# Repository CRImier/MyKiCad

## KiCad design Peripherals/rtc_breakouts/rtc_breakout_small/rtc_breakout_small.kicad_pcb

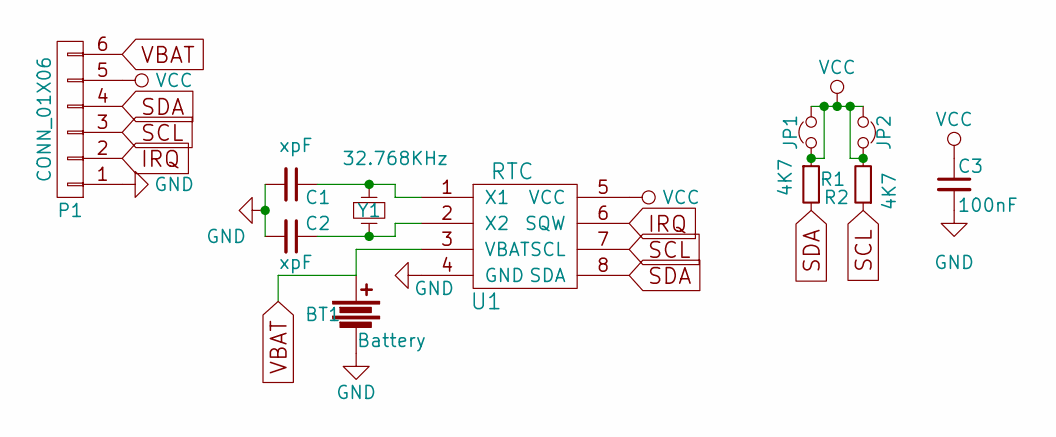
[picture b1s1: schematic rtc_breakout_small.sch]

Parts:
BT1: Battery; CR2032H
C1, C2: xpF; C_0603_HandSoldering
C3: 100nF; C_0603_HandSoldering
JP1, JP2: Jumper_NC_Small; GS2_SMALL
P1: CONN_01X06; Pin_Header_Straight_1x06_Pitch2.54mm
R1, R2: 4K7; R_0603_HandSoldering
U1: RTC; SOIC-8_3.9x4.9mm_Pitch1.27mm
Y1: 32.768KHz; Crystal_SMD_G8-2pin_3.2x1.5mm_HandSoldering

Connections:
GND: BT1.2, C1.2, C2.2, C3.2, P1.1, U1.4 (GND)
IRQ: P1.2, U1.6 (SQW)
unnamed: C1.1, U1.1 (X1), Y1.1
unnamed: C2.1, U1.2 (X2), Y1.2
SCL: P1.3, R2.1, U1.7 (SCL)
SDA: P1.4, R1.2, U1.8 (SDA)
VBAT: BT1.1, P1.6, U1.3 (VBAT)
VCC: C3.1, JP1.1, JP1.2, JP2.1, JP2.2, P1.5, R1.1, R2.2, U1.5 (VCC)

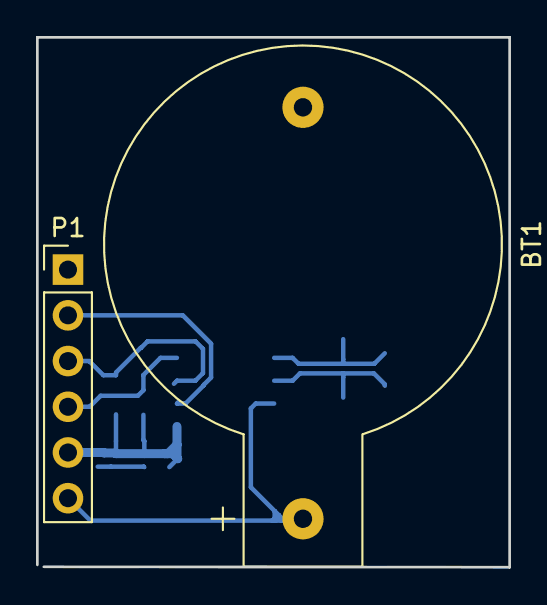
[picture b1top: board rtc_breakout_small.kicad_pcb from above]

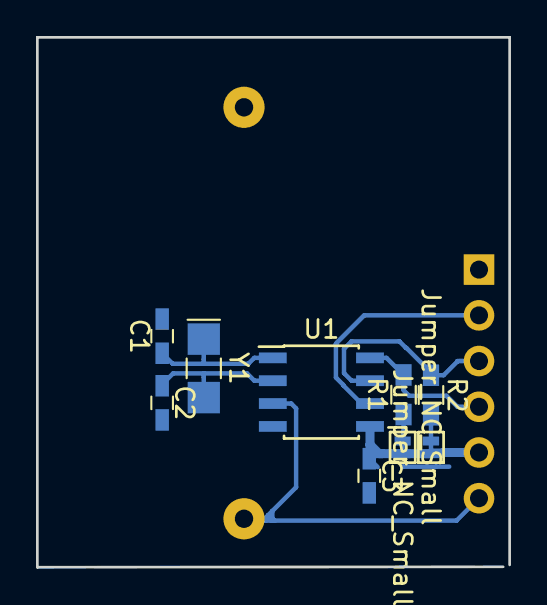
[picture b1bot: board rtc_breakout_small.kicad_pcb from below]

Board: 2 copper layers, 26.2 x 29.4 mm, 11 parts (9 on the bottom side), 8 nets.

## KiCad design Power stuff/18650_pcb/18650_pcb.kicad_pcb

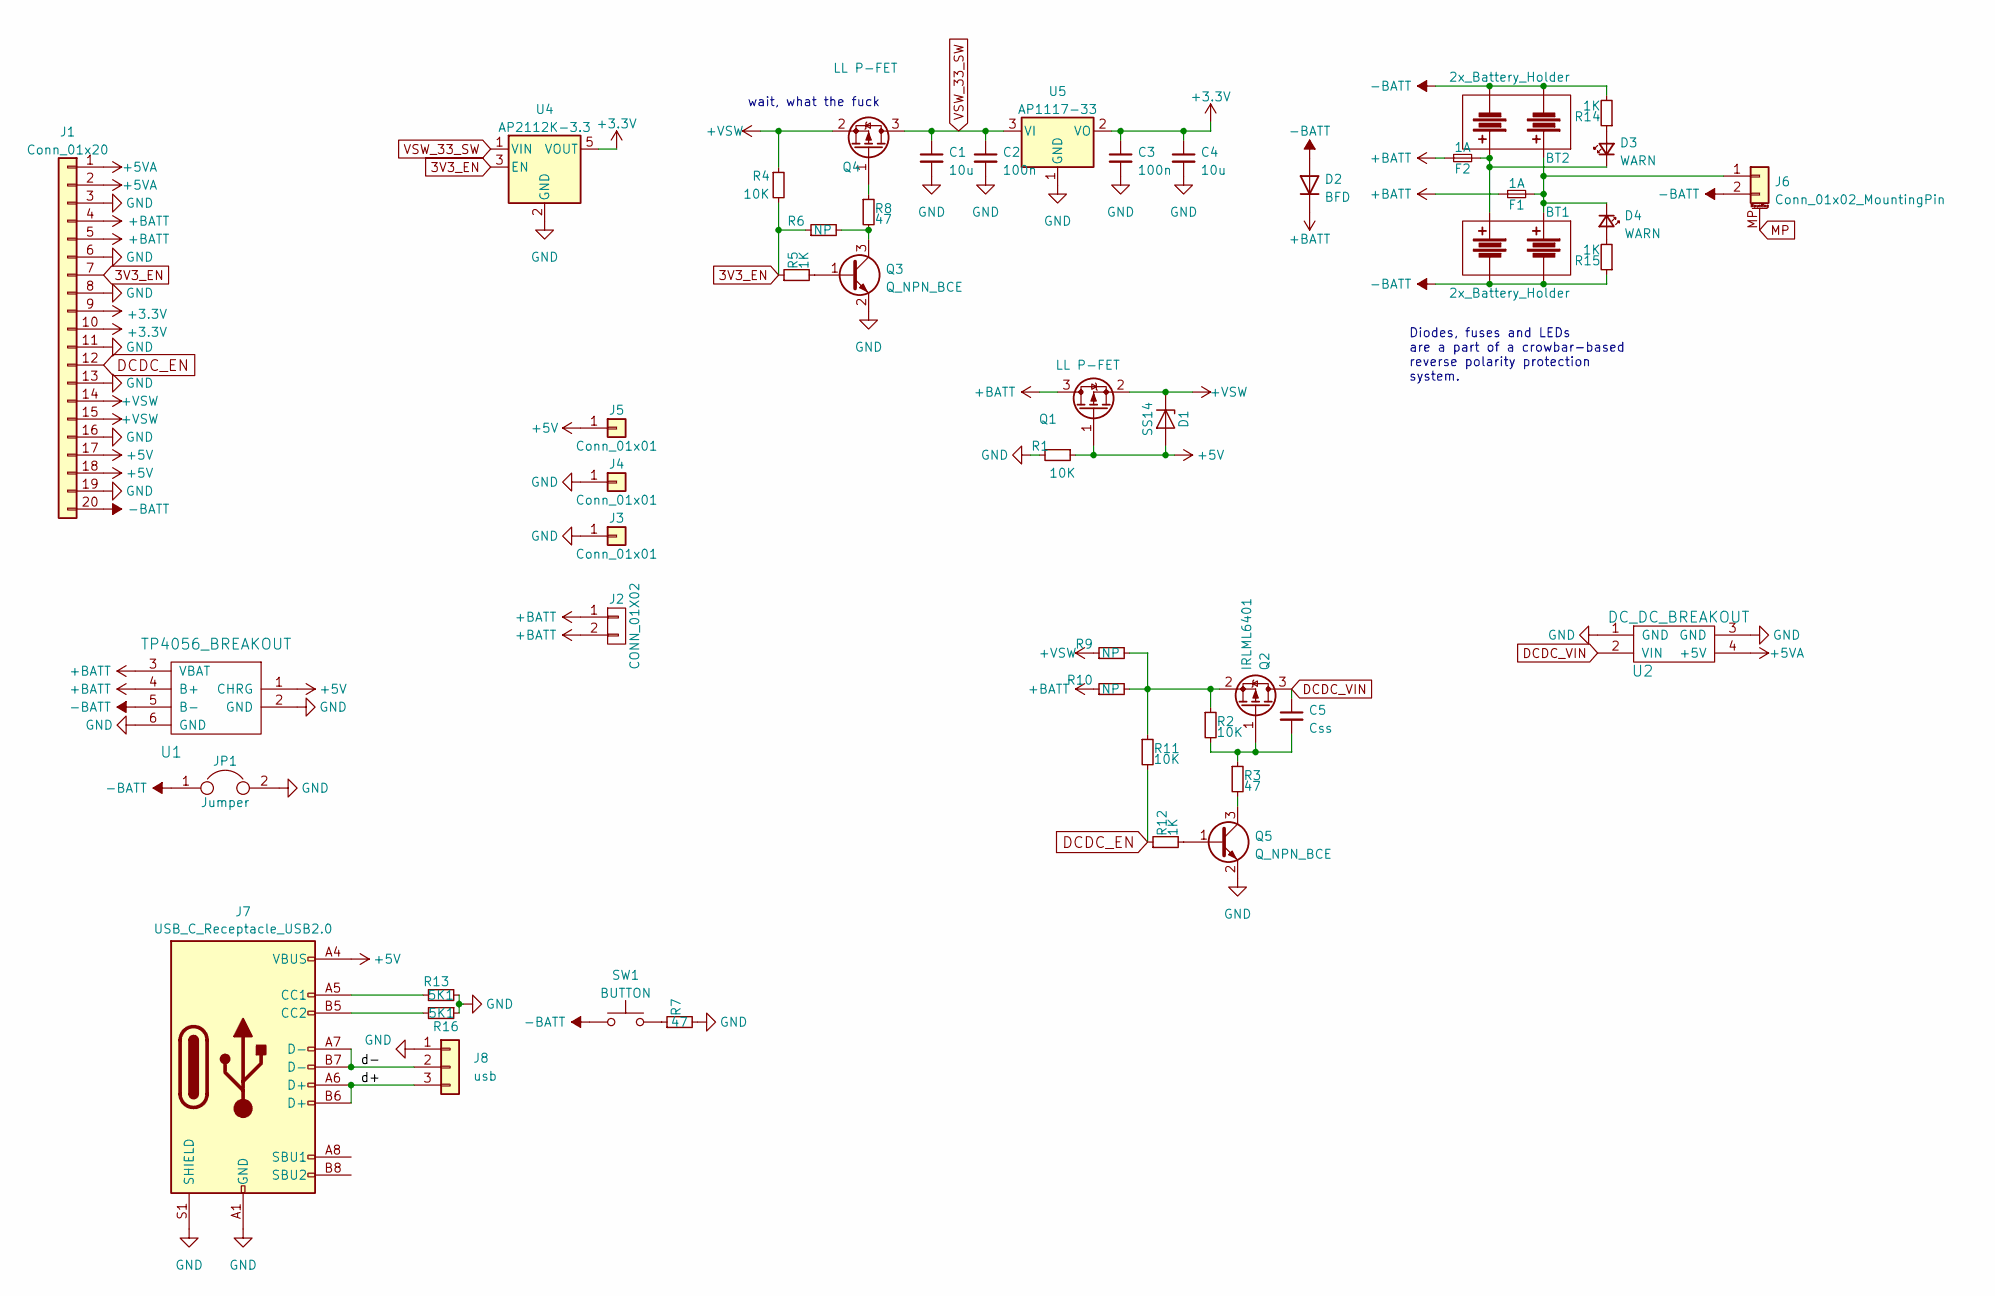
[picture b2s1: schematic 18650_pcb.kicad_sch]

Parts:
BT1: 2x_Battery_Holder; KEYSTONE_1048
BT2: 2x_Battery_Holder; BLM_18650_PC4
C1, C4: 10u; C_0805_2012Metric
C2, C3: 100n; C_0805_2012Metric
C5: Css; C_0805_2012Metric
D1: SS14; D_SMA_Handsoldering
D2: BFD; D_SMC-RM10_Universal_Handsoldering
D3, D4: WARN; LED_0805_2012Metric
F1, F2: 1A; Fuse_2010_5025Metric_Pad1.52x2.65mm_HandSolder
J1: Conn_01x20; PinHeader_1x20_P2.54mm_Vertical
J2: CONN_01X02; PinHeader_1x02_P2.54mm_Vertical
J3, J4, J5: Conn_01x01; PinHeader_1x01_P2.54mm_Vertical
J6: Conn_01x02_MountingPin; JST_PH_S2B-PH-SM4-TB_02x2.00mm_Angled
J7: USB_C_Receptacle_USB2.0; USB_C_Receptacle_HRO_TYPE-C-31-M-12
J8: usb; PinHeader_1x03_P2.54mm_Vertical
JP1: Jumper; GS2
Q1, Q4: LL P-FET; SOT-23
Q2: IRLML6401; SOT-23
Q3, Q5: Q_NPN_BCE; SOT-23
R1, R2, R4, R11: 10K; R_0805_2012Metric
R3, R7, R8: 47; R_0805_2012Metric
R5, R12, R14, R15: 1K; R_0805_2012Metric
R6, R9, R10: NP; R_0805_2012Metric
R13, R16: 5K1; R_0805_2012Metric
SW1: BUTTON; Switch_Side_Vertical_Combined
U1: TP4056_BREAKOUT
U2: DC_DC_BREAKOUT; DC-DC-BREAKOUT
U4: AP2112K-3.3; SOT-23-5
U5: AP1117-33; SOT-223-3_TabPin2

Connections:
3V3_EN: J1.7, R4.2, R5.1, R6.1, U4.3 (EN)
+3.3V: C3.1, C4.1, J1.9, J1.10, U4.5 (VOUT), U5.2 (VO)
+5V: D1.2 (A), J1.17, J1.18, J5.1, J7.A4 (VBUS), J7.A9 (VBUS), J7.B4 (VBUS), J7.B9 (VBUS), Q1.1 (G), R1.1, U1.1 (CHRG)
+5VA: J1.1, J1.2, U2.4 (+5V)
+BATT: D2.1 (K), F1.1, F2.1, J1.4, J1.5, J2.1, J2.2, Q1.3 (D), R10.1, U1.3 (VBAT), U1.4 (B+)
+VSW: D1.1 (K), J1.14, J1.15, Q1.2 (S), Q4.2 (S), R4.1, R9.1
-BATT: BT1.3, BT1.4, BT2.3, BT2.4, D2.2 (A), J1.20, J6.2, JP1.1, R14.2, R15.1, SW1.1, U1.5 (B-)
/d+: J7.A6 (D+), J7.B6 (D+), J8.3
/d-: J7.A7 (D-), J7.B7 (D-), J8.2
DCDC_EN: J1.12, R11.2, R12.1
DCDC_VIN: C5.1, Q2.3 (D), U2.2 (VIN)
GND: C1.2, C2.2, C3.2, C4.2, J1.3, J1.6, J1.8, J1.11, J1.13, J1.16, J1.19, J3.1, J4.1, J7.A1 (GND), J7.A12 (GND), J7.B1 (GND), J7.B12 (GND), J7.S1 (SHIELD), J8.1, JP1.2, Q3.2 (E), Q5.2 (E), R1.2, R7.2, R13.2, R16.1, U1.2 (GND), U1.6 (GND), U2.1 (GND), U2.3 (GND), U4.2 (GND), U5.1 (GND)
MP: J6.MP (MountPin)
unnamed: D3.2 (A), R14.1
unnamed: BT1.2, BT2.2, D3.1 (K), F2.2
unnamed: D4.2 (A), R15.2
unnamed: BT1.1, BT2.1, D4.1 (K), F1.2, J6.1
unnamed: J7.A5 (CC1), R13.1
unnamed: J7.B5 (CC2), R16.2
unnamed: C5.2, Q2.1 (G), R2.2, R3.1
unnamed: Q2.2 (S), R2.1, R9.2, R10.2, R11.1
unnamed: Q3.1 (B), R5.2
unnamed: Q3.3 (C), R6.2, R8.2
unnamed: Q4.1 (G), R8.1
unnamed: Q5.1 (B), R12.2
unnamed: Q5.3 (C), R3.2
unnamed: R7.1, SW1.2
VSW_33_SW: C1.1, C2.1, Q4.3 (D), U4.1 (VIN), U5.3 (VI)

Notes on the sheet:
wait, what the fuck
Diodes, fuses and LEDs are a part of a crowbar-based reverse polarity protection system.

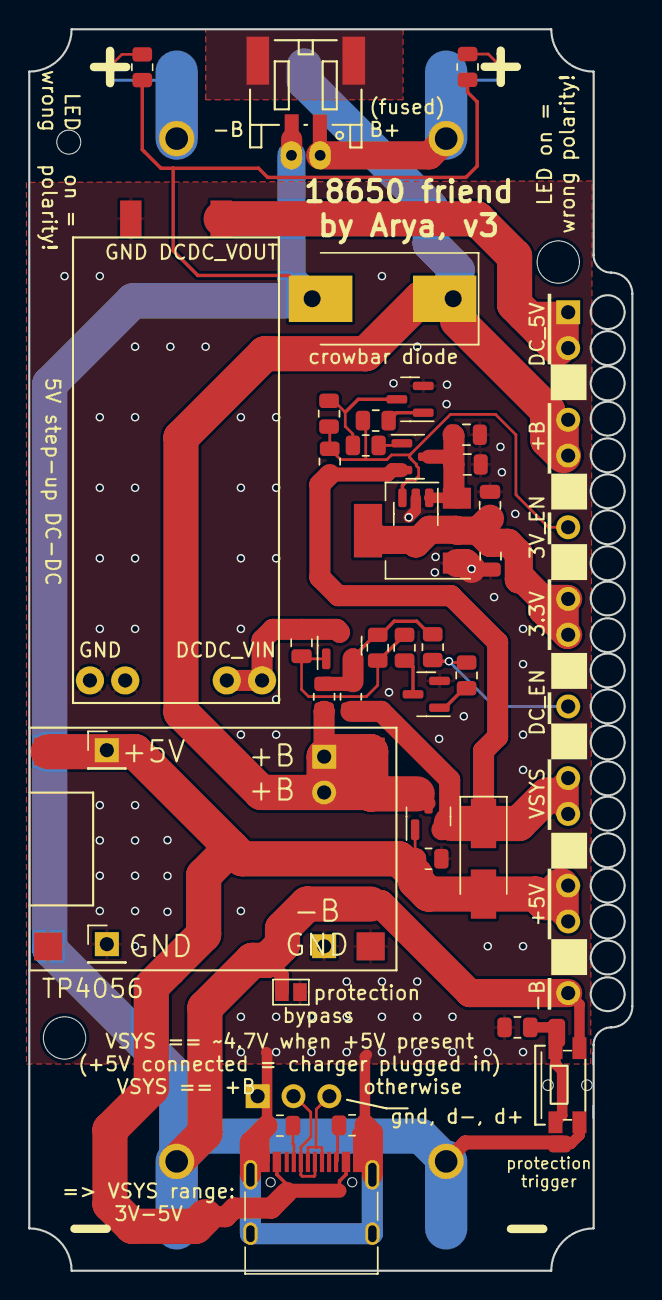
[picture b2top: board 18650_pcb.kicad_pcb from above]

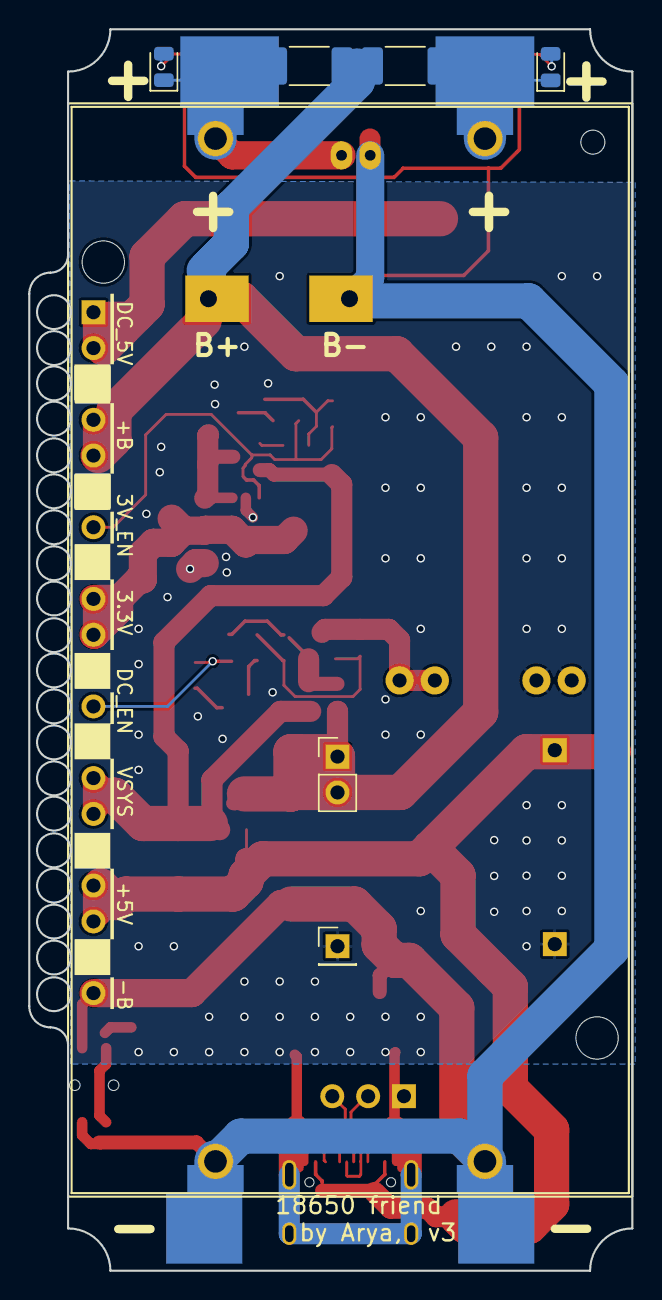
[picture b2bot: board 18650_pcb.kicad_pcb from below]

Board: 2 copper layers, 42.8 x 88.0 mm, 48 parts (9 on the bottom side), 27 nets.

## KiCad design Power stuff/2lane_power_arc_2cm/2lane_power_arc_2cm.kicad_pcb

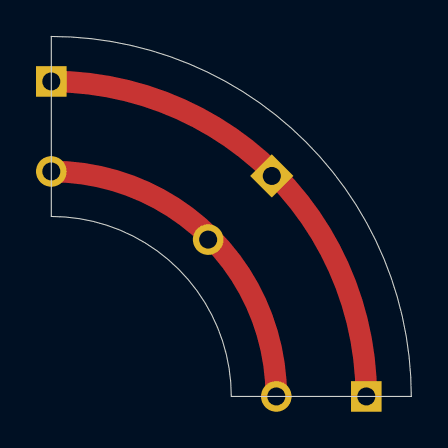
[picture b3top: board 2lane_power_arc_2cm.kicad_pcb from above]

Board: 2 copper layers, 20.0 x 20.0 mm, 3 parts (0 on the bottom side), 2 nets, no tracks yet.

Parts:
J1, J2, J3: C; PinHeader_1x02_P2.54mm_Vertical

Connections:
unnamed: J1.1, J2.1, J3.1
unnamed: J1.2, J2.2, J3.2

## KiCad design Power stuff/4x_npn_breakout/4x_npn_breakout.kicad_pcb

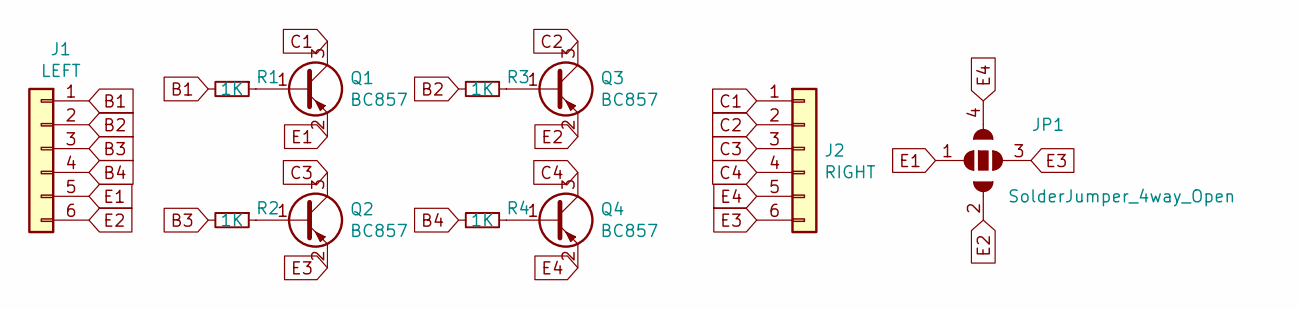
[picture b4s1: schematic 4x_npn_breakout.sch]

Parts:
J1: LEFT; PinHeader_1x06_P2.54mm_Vertical
J2: RIGHT; PinHeader_1x06_P2.54mm_Vertical
JP1: SolderJumper_4way_Open; 4Way_Jumper
Q1, Q2, Q3, Q4: BC857; SOT-23
R1, R2, R3, R4: 1K; R_0805_2012Metric

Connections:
B1: J1.1, R1.2
B2: J1.2, R3.2
B3: J1.3, R2.2
B4: J1.4, R4.2
C1: J2.1, Q1.3 (C)
C2: J2.2, Q3.3 (C)
C3: J2.3, Q2.3 (C)
C4: J2.4, Q4.3 (C)
E1: J1.5, JP1.1 (A), Q1.2 (E)
E2: J1.6, JP1.2 (C), Q3.2 (E)
E3: J2.6, JP1.3 (B), Q2.2 (E)
E4: J2.5, JP1.4 (D), Q4.2 (E)
unnamed: Q1.1 (B), R1.1
unnamed: Q2.1 (B), R2.1
unnamed: Q3.1 (B), R3.1
unnamed: Q4.1 (B), R4.1

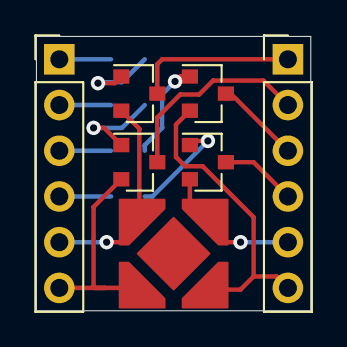
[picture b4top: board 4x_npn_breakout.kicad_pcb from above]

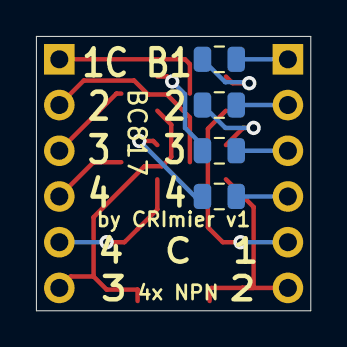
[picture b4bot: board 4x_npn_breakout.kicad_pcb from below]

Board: 2 copper layers, 15.2 x 15.2 mm, 11 parts (4 on the bottom side), 16 nets.

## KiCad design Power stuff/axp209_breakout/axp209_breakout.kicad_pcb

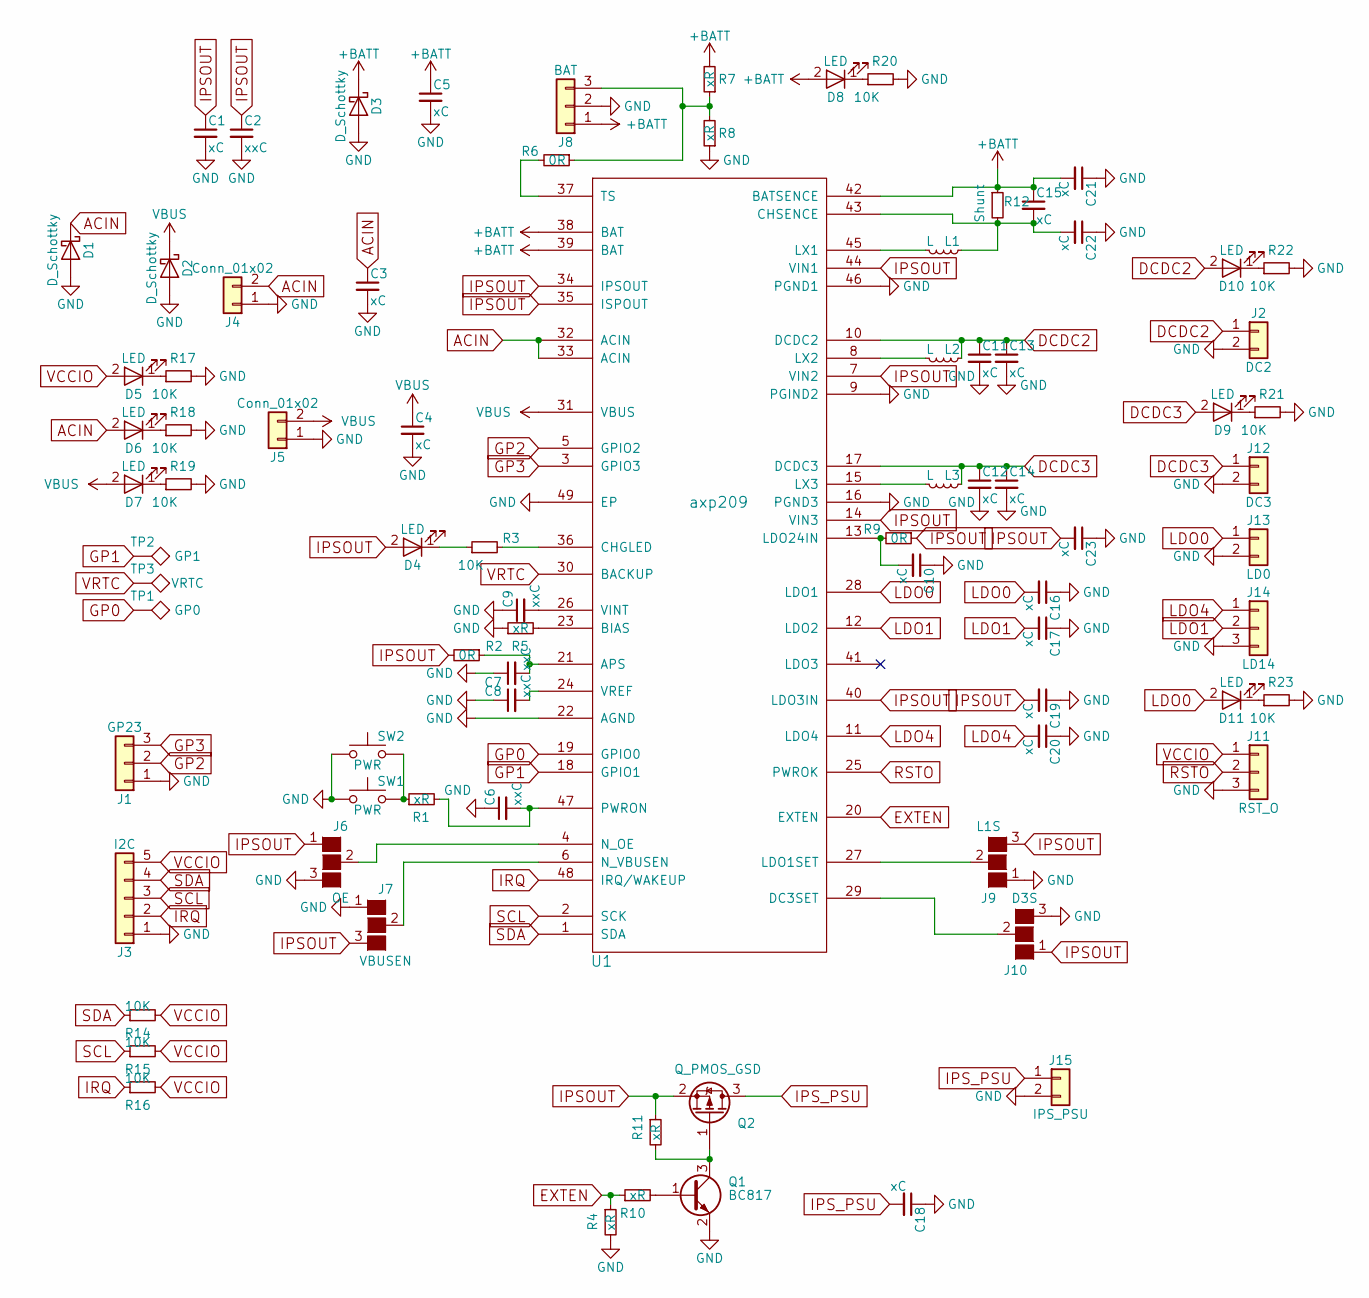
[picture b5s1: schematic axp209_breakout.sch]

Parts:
C1, C3, C4, C5, C10, C11, C12, C13, C14, C15, C16, C17, C18, C19, C20, C21, C22, C23: xC; C_0805
C2, C6, C7, C8, C9: xxC; C_0603
D1, D2, D3: D_Schottky; D_SMA
D4, D5, D6, D7, D8, D9, D10, D11: LED; LED_0805
J1: GP23; Pin_Header_Straight_1x03_Pitch2.00mm
J2: DC2; Pin_Header_Straight_1x02_Pitch2.54mm
J3: I2C; Pin_Header_Straight_1x05_Pitch2.54mm
J4, J5: Conn_01x02; Pin_Header_Straight_1x02_Pitch2.54mm
J6: OE; GS3_SMALL
J7: VBUSEN; GS3_SMALL
J8: BAT; JST_PH_S3B-PH-K_03x2.00mm_Angled
J9: L1S; GS3_SMALL
J10: D3S; GS3_SMALL
J11: RST_O; Pin_Header_Straight_1x03_Pitch2.00mm
J12: DC3; Pin_Header_Straight_1x02_Pitch2.54mm
J13: LD0; Pin_Header_Straight_1x02_Pitch2.54mm
J14: LD14; Pin_Header_Straight_1x03_Pitch2.54mm
J15: IPS_PSU; Pin_Header_Straight_1x02_Pitch2.54mm
L1, L2, L3: L; Inductor_Taiyo-Yuden_NR-40xx
Q1: BC817; SOT-23
Q2: Q_PMOS_GSD; SOT-23
R1, R4, R5, R7, R8, R10, R11: xR; R_0603
R2, R6, R9: 0R; R_0402
R3, R17, R18, R19, R20, R21, R22, R23: 10K; R_0402
R12: Shunt; R_MELF_MMB-0207
R14, R15, R16: 10K; R_0603
SW1, SW2: PWR; SW_SPST_EVQPE1
TP1: GP0; Measurement_Point_Round-SMD-Pad_VerySmall
TP2: GP1; Measurement_Point_Round-SMD-Pad_VerySmall
TP3: VRTC; Measurement_Point_Round-SMD-Pad_VerySmall
U1: axp209; TQFP-48-1EP_6x6mm_Pitch0.4mm

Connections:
+BATT: C5.1, C15.1, C21.2, D3.1 (K), D8.2 (A), J8.1, R7.2, R12.1, U1.38 (BAT), U1.39 (BAT), U1.42 (BATSENCE)
ACIN: C3.1, D1.1 (K), D6.2 (A), J4.2, U1.32 (ACIN), U1.33 (ACIN)
DCDC2: C11.1, C13.1, D10.2 (A), J2.1, L2.1, U1.10 (DCDC2)
DCDC3: C12.1, C14.1, D9.2 (A), J12.1, L3.1, U1.17 (DCDC3)
EXTEN: R4.1, R10.1, U1.20 (EXTEN)
GND: C1.2, C2.2, C3.2, C4.2, C5.2, C6.1, C7.1, C8.1, C9.1, C10.1, C11.2, C12.2, C13.2, C14.2, C16.1, C17.1, C18.1, C19.1, C20.1, C21.1, C22.1, C23.1, D1.2 (A), D2.2 (A), D3.2 (A), J1.1, J2.2, J3.1, J4.1, J5.1, J6.3 (G3), J7.1 (G1), J8.2, J9.1 (G1), J10.3 (G3), J11.3, J12.2, J13.2, J14.3, J15.2, Q1.2 (E), R4.2, R5.1, R8.1, R17.2, R18.2, R19.2, R20.2, R21.2, R22.2, R23.2, SW1.1, SW2.1, U1.9 (PGIND2), U1.16 (PGND3), U1.22 (AGND), U1.46 (PGND1), U1.49 (EP)
GP0: TP1.1, U1.19 (GPIO0)
GP1: TP2.1, U1.18 (GPIO1)
GP2: J1.2, U1.5 (GPIO2)
GP3: J1.3, U1.3 (GPIO3)
IPSOUT: C1.1, C2.1, C19.2, C23.2, D4.2 (A), J6.1 (G1), J7.3 (G3), J9.3 (G3), J10.1 (G1), Q2.2 (S), R2.2, R9.1, R11.1, U1.7 (VIN2), U1.14 (VIN3), U1.34 (IPSOUT), U1.35 (ISPOUT), U1.40 (LDO3IN), U1.44 (VIN1)
IPS_PSU: C18.2, J15.1, Q2.3 (D)
IRQ: J3.2, R16.1, U1.48 (IRQ/WAKEUP)
LDO0: C16.2, D11.2 (A), J13.1, U1.28 (LDO1)
LDO1: C17.2, J14.2, U1.12 (LDO2)
LDO4: C20.2, J14.1, U1.11 (LDO4)
unnamed: C6.2, R1.2, U1.47 (PWRON)
unnamed: C7.2, R2.1, U1.21 (APS)
unnamed: C8.2, U1.24 (VREF)
unnamed: C9.2, U1.26 (VINT)
unnamed: C10.2, R9.2, U1.13 (LDO24IN)
unnamed: C15.2, C22.2, L1.1, R12.2, U1.43 (CHSENCE)
unnamed: D4.1 (K), R3.1
unnamed: D5.1 (K), R17.1
unnamed: D6.1 (K), R18.1
unnamed: D7.1 (K), R19.1
unnamed: D8.1 (K), R20.1
unnamed: D9.1 (K), R21.1
unnamed: D10.1 (K), R22.1
unnamed: D11.1 (K), R23.1
unnamed: J6.2 (G2), U1.4 (N_OE)
unnamed: J7.2 (G2), U1.6 (N_VBUSEN)
unnamed: J8.3, R6.1, R7.1, R8.2
unnamed: J9.2 (G2), U1.27 (LDO1SET)
unnamed: J10.2 (G2), U1.29 (DC3SET)
unnamed: L1.2, U1.45 (LX1)
unnamed: L2.2, U1.8 (LX2)
unnamed: L3.2, U1.15 (LX3)
unnamed: Q1.1 (B), R10.2
unnamed: Q1.3 (C), Q2.1 (G), R11.2
unnamed: R1.1, SW1.2, SW2.2
unnamed: R3.2, U1.36 (CHGLED)
unnamed: R5.2, U1.23 (BIAS)
unnamed: R6.2, U1.37 (TS)
RSTO: J11.2, U1.25 (PWROK)
SCL: J3.3, R15.1, U1.2 (SCK)
SDA: J3.4, R14.1, U1.1 (SDA)
VBUS: C4.1, D2.1 (K), D7.2 (A), J5.2, U1.31 (VBUS)
VCCIO: D5.2 (A), J3.5, J11.1, R14.2, R15.2, R16.2
VRTC: TP3.1, U1.30 (BACKUP)

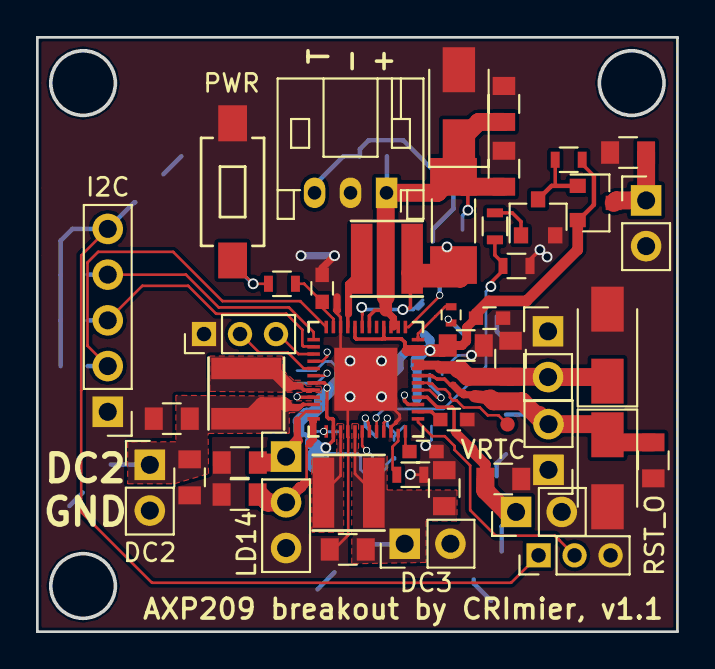
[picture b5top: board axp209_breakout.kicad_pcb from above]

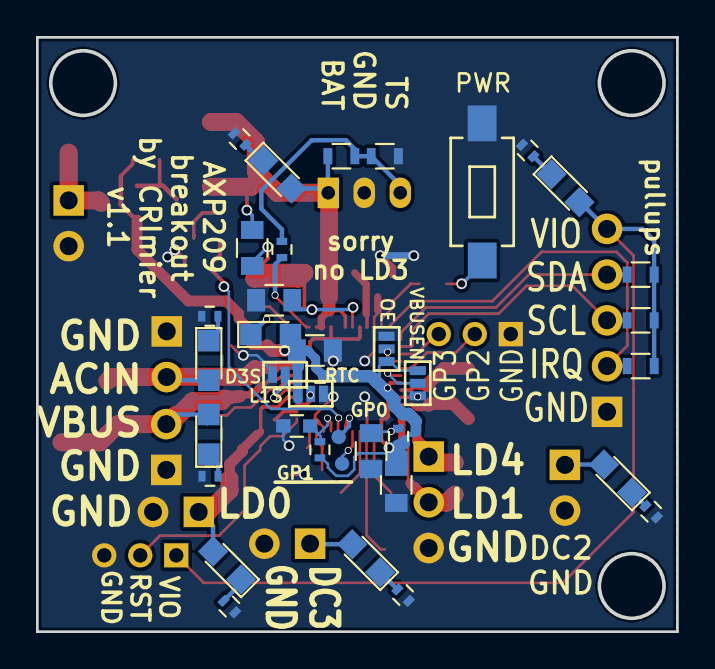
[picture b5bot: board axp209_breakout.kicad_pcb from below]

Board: 2 copper layers, 35.6 x 33.0 mm, 82 parts (36 on the bottom side), 50 nets.
